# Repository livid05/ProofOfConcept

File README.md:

<div align="center">

# Per-Key Precision

### A fast, low-power TMR analog keyboard on the STM32U5A5

From an RP2040 QMK macro pad to a from-scratch firmware, with every board, measurement and mistake written down.

[Quick start](#quick-start) | [Results](#results-so-far) | [The boards](#the-boards) | [Docs](#find-what-you-need) | [Roadmap](#whats-next) | [License](#license)

</div>

---

## What this is

A capstone project to build a keyboard that senses how far each key is pressed, using TMR (tunnel magnetoresistance) sensors, and reports it to a PC over USB at 8 kHz. The firmware is written from scratch for an STM32U5A5, replacing an earlier QMK proof of concept on an RP2040. The goals are speed, a reliable connection, low power draw and a robust feature set.

This repository holds everything: the firmware, the KiCad hardware for every board revision, the bench results, the research, the presentations, and the reasoning behind each decision.

## How it works

```mermaid
flowchart LR
    A[15 TMR2615D sensors] --> B[CD74HC4067 analog mux]
    B --> C[RC filter 100 ohm + 4.7 nF]
    C --> D[STM32U5A5 ADC1 on PC4]
    D --> E[Press logic and rapid trigger]
    E --> F[USB HID, 8 kHz]
    F --> G[PC]
```

Each sensor outputs a voltage that moves as a magnet gets closer. One 16-way mux feeds a single ADC pin, so the firmware scans the keys one after another. At 8 kHz a full scan has to finish in 125 microseconds. The simple blocking scan takes 730 microseconds for 16 inputs, so a faster pipelined scan has been written; it is the next thing to test on the board. [How the sensing works](docs/03-tmr-sensing-guide.md) explains the details in plain language.

## Results so far

| What | Result | Status |
|---|---|---|
| USB report rate | 7999 reports per second, 0 dropped in 10 seconds | Measured on a PC |
| TMR numpad self-test | 14 of 15 keys pass | Observed on the bench; key K4 is open and parked |
| Blocking scan time | 730 microseconds for 16 inputs | Measured; too slow for 8 kHz |
| Fast pipelined scan with rapid trigger | Written, passes PC tests and a syntax check | Not yet built for the board or run on hardware |
| Full tri-mode keyboard (TriMode60) | Designed through Rev E | Design only, not built |

Things marked as not yet run have not been observed on hardware. The docs keep that difference on purpose. The [bench write-up](docs/04-bench-bringup-2026-11-18.md) has the numbers and how each problem was found.

## The boards

| Board | Purpose | Layers | Status |
|---|---|---|---|
| [Dev board Rev K](hardware/devboard-u5a5/RevK/) | STM32U5A5 development board with USB-C, SWD, a 16-channel mux and a sensor header | 4 | Built and in use |
| [Numpad TMR1 Rev E](hardware/numpad-tmr/RevE/) | 15 TMR sensors in a numpad layout, wired to the dev board | 2 | Built, 14 of 15 keys pass |
| [TriMode60 Rev E](hardware/trimode60/RevE/) | 61 sensors, USB, Bluetooth LE and 2.4 GHz radio in one board | 4 | Designed, not built |

Every revision of every board has notes on what changed and why, with before and after pictures, in [Hardware evolution](docs/02-hardware-evolution.md).

## Quick start

You need a Windows PC with STM32CubeIDE installed (the scripts use the compiler and tools that come with it), VS Code, and the dev board plus numpad.

**1. Build the firmware**

```powershell
cd stm32u5a5-keypad
.\tools\build.ps1
```

**2. Flash over USB**

Connect the dev board with a data cable, hold BOOT, tap RST, release BOOT, then:

```powershell
.\tools\flash-usb.ps1
```

Press RST afterwards. Prebuilt images are in [`binaries/`](binaries/) if you only want to flash.

**3. Run the PC tests (no board needed)**

```powershell
.\tools\test-host.ps1
```

**4. Try the TMR fast-scan image** (not yet run on hardware)

```powershell
cd future_work\2026-11-18_tmr_fast\tools
.\build-tmr-fast.ps1
.\flash-tmr-fast-usb.ps1
.\tmr-console.ps1
```

In the console press `t` for the self-test, then `x` for the sweep that measures noise. Full steps, ports and troubleshooting are in the [Build, flash and test guide](docs/05-build-flash-test-guide.md).

## Find what you need

| I want to... | Read |
|---|---|
| Understand the whole story | [Project story](docs/01-project-story.md) |
| See how the boards changed | [Hardware evolution](docs/02-hardware-evolution.md) |
| Learn how the sensors and ADC work | [TMR sensing guide](docs/03-tmr-sensing-guide.md) |
| See what was measured and what broke | [Bench bring-up](docs/04-bench-bringup-2026-11-18.md) |
| Build, flash and test | [Build, flash and test guide](docs/05-build-flash-test-guide.md) |
| Compare with other 8K TMR keyboards | [8 kHz scanning and market research](docs/06-8k-scanning-and-market-research.md) |
| Know what comes next | [Roadmap](docs/07-roadmap.md) |
| Avoid my mistakes | [Lessons learned](docs/08-lessons-learned.md) |
| Open or order the KiCad boards | [KiCad guide](docs/09-kicad-guide.md) |
| Find a presentation or report | [Presentations and reports](docs/10-presentations-and-reports.md) |
| See how it started on the RP2040 | [RP2040 proof of concept](docs/rp2040-proof-of-concept.md) |

## What is in the repository

| Folder | Contents |
|---|---|
| [`stm32u5a5-keypad/`](stm32u5a5-keypad/) | The firmware, PC tests, build tools and the diagnostic test images. Its `docs/STATUS.md` is the day-to-day status |
| [`hardware/`](hardware/) | KiCad projects, production files and revision notes for all three boards |
| [`docs/`](docs/) | The guides listed above |
| [`reports/`](reports/) | Presentations, the Rev H overview, instructor feedback and the capstone deck source |
| [`binaries/`](binaries/) | Prebuilt `.bin` and `.hex` images of each verified step |
| [`cubemx/`](cubemx/) | STM32CubeMX configuration files |
| [`rp2040-reference/`](rp2040-reference/) | Material from the RP2040 stage |
| Repo root, [`ble_bridge/`](ble_bridge/), [`esb_bridge/`](esb_bridge/), [`esb_dongle/`](esb_dongle/), [`schematics/`](schematics/) | The original RP2040 QMK keypad, its wireless bridges and early schematics |

## What's next

1. Replace the open sensor on key K4 and recheck columns 3 and 4 of the matrix.
2. Build and run the fast scan image on the board, then read the noise sweep.
3. Tune the press thresholds and rapid trigger from real data.
4. Add low-power modes and measure current draw.
5. Build TriMode60 and bring up the radio.

The full ordered list, with reasons, is in the [Roadmap](docs/07-roadmap.md).

## License

Code and hardware designs are MIT, documentation and images are CC BY 4.0, and the reports in `reports/` are all rights reserved. ST and Arm code keeps its own licenses, and the QMK-based RP2040 files are GPL-2.0-or-later. The USB ID 0483:5710 used for bench work is ST's demonstration ID and must be replaced before any product is shared or sold. The exact terms are in [`LICENSE`](LICENSE).

<div align="center">

Made by Tyler Judkins, computer engineering technology, Central Connecticut State University

</div>

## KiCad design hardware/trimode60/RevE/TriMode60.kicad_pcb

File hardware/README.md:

# Hardware

KiCad projects, production files and revision notes. Open the `.kicad_pro` files in KiCad 9 or later. Library tables and the custom TMR2615D symbol and footprint are included with the numpad project.

## Latest revisions

| Folder | Board | Revision | Notes |
|---|---|---|---|
| `devboard-u5a5/RevK/` | STM32U5A5 development board, 4 layers, on-board 16:1 mux and 2x10 sensor header (J8), USB-C high speed | K | `production/` holds gerbers, BOM and positions. Read `README_REVK.txt` first |
| `numpad-tmr/RevE/` | 15-key TMR numpad, 2 layers, hot-swap MX sockets, SK6812 LEDs | E | Production variants: `production`, `production_economic`, `production_economic_handsolder`, `production_jlc_fixed`; each has a README |
| `trimode60/RevE/` | 60% tri-mode keyboard (STM32U595, nRF52840 module, charger, PD sink), 4 layers | E | Design only. Per-sheet schematics: `mcu`, `power`, `keys`, `radio`. Renders in `renders/` |

Hand-solder parts are listed in each board's README (for the dev board: J2, J3, J8, J9, J10; for the numpad: J1, J2, J3). The sensors (U1 to U15 on the numpad) have no LCSC number and are fitted by hand.

## History

[`history/`](history/) holds the README or change notes for each earlier revision (dev board B to J, numpad B to D, TriMode60 A to D, and the panel experiment). They are the source for [docs/02-hardware-evolution.md](../docs/02-hardware-evolution.md).

## Images

[`images/`](images/) holds layout comparisons and renders exported from the KiCad projects during each revision, grouped by board.

| Image | Shows |
|---|---|
| `images/devboard/RevB_layout.png`, `RevC_layout.png`, `RevD_layout.png` | Early layouts: MCU move, on-board mux, stabilizer pins |
| `images/devboard/RevI_vs_RevH_top.png`, `RevJ_vs_RevI_USB.png`, `RevH_UART_before_after.png` | Later layout changes |
| `images/numpad/sensor_before_after.png`, `vip_cleanup_before_after.png`, `vip_cleanup_details.png`, `j2_check.png` | Sensor footprint fix and via-in-pad cleanup |
| `images/trimode60/TriMode60_*.png` | 3D renders and copper layers of Rev E |
| `images/panel/RENDER_top.png`, `RENDER_bottom.png` | The dev board plus numpad panel experiment |

These are not schematic exports. To get schematic PDFs or fresh board renders, run KiCad's export on the projects above.

## Earlier work

The `schematics/` folder at the repository root holds the earlier KiCad projects from the RP2040 stage (capstone design, matrix and mux, numpad TMR1 first version). They are kept for the record; the folders here supersede them.

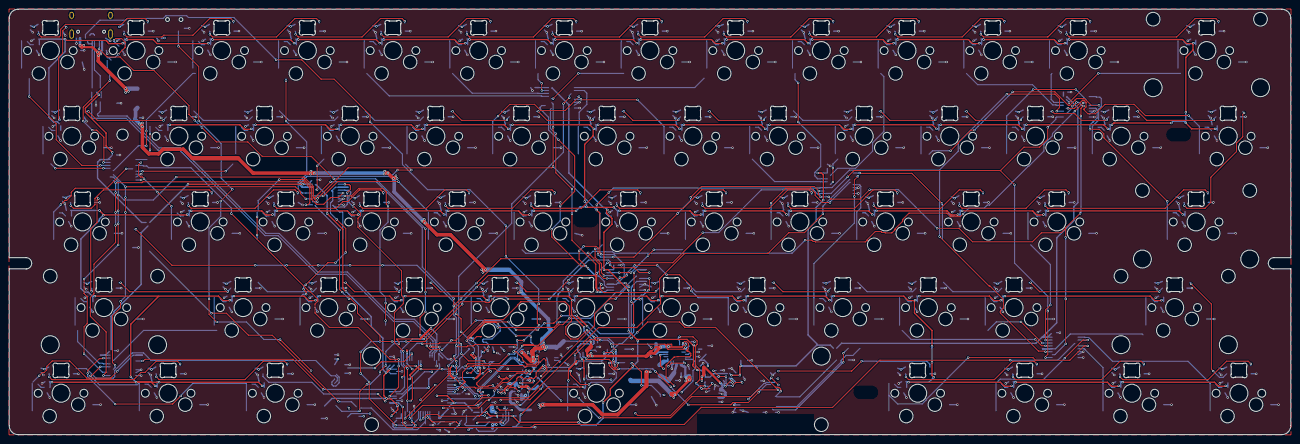
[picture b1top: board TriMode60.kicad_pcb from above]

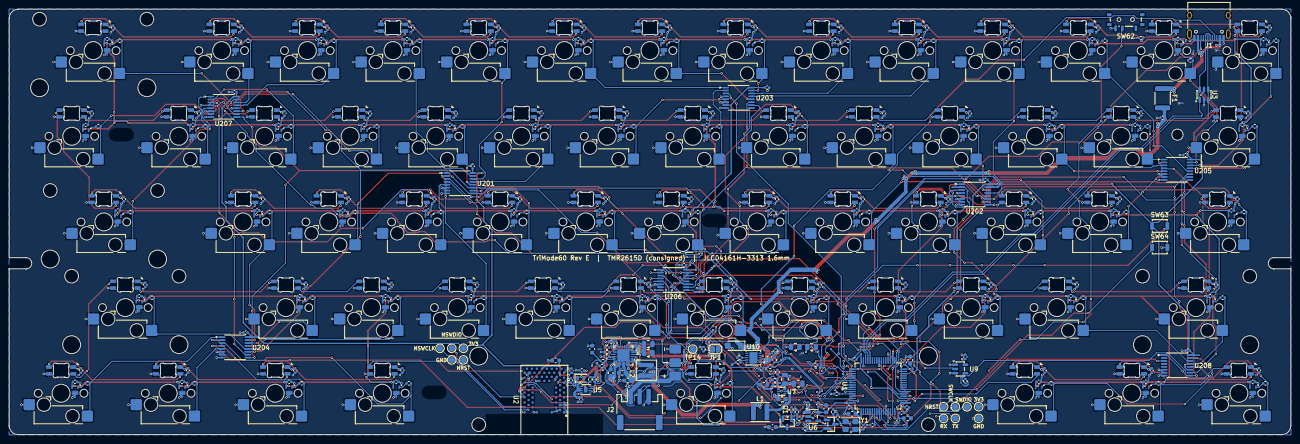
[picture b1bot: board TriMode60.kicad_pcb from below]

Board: 4 copper layers, 285.0 x 94.6 mm, 492 parts (483 on the bottom side), 252 nets.

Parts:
BAT_OUTLINE: LiPo 606090 4000mAh (fit check); Battery_LiPo_606090_Outline
C1, C2, C5, C6, C7, C25, C38, C44: 1uF; C_0402_1005Metric
C3, C4, C8, C9, C15, C32, C41: 10uF; C_0603_1608Metric
C10, C11, C13, C14: 22uF; C_0805_2012Metric
C20, C21, C22, C23, C26, C28, C31, C33, C37, C101, C102, C103, C104, C105, C106, C107, C108, C109, C110, C111, C112, C113, C114, C115, C116, C117, C118, C119, C120, C121, C122, C123, C124, C125, C126, C127, C128, C129, C130, C131, C132, C133, C134, C135, C136, C137, C138, C139, C140, C141, C142, C143, C144, C145, C146, C147, C148, C149, C150, C151, C152, C153, C154, C155, C156, C157, C158, C159, C160, C161, C201, C202, C203, C204, C205, C206, C207, C208, C209, C210, C211, C212, C213, C214, C215, C216, C217, C218, C219, C220, C221, C222, C223, C224, C225, C226, C227, C228, C229, C230, C231, C232, C233, C234, C235, C236, C237, C238, C239, C240, C241, C242, C243, C244, C245, C246, C247, C248, C249, C250, C251, C252, C253, C254, C255, C256, C257, C258, C259, C260, C261, C301, C302, C303, C304, C305, C306, C307, C308: 100nF; C_0402_1005Metric
C24, C27, C42: 4.7uF; C_0603_1608Metric
C29, C30: 12pF; C_0402_1005Metric
C34, C35: 20pF; C_0402_1005Metric
C36: 150pF; C_0603_1608Metric
C39, C40: 10uF 25V; C_0805_2012Metric
C43: 47nF; C_0402_1005Metric
D1, D2, D3, D4, D5, D6, D7, D8, D9, D10, D11, D12, D13, D14, D15, D16, D17, D18, D19, D20, D21, D22, D23, D24, D25, D26, D27, D28, D29, D30, D31, D32, D33, D34, D35, D36, D37, D38, D39, D40, D41, D42, D43, D44, D45, D46, D47, D48, D49, D50, D51, D52, D53, D54, D55, D56, D57, D58, D59, D60, D61: SK6812MINI-E; LED_SK6812MINI-E_Reverse
D62: BAT54C; SOT-23
D63: SMF12A; D_SMF
F1: PTC 3A hold; Fuse_1812_4532Metric
FB1: 600R@100MHz; L_0603_1608Metric
H1: MountingHole_2.5mm_NPTH
H2, H3, H4: MountingSlot_5.0x2.5mm_NPTH
J1: USB-C 16P; USB_C_Receptacle_HRO_TYPE-C-31-M-12
J2: Battery JST-PH 3P; JST_PH_S3B-PH-SM4-TB_1x03-1MP_P2.00mm_Horizontal
J3: Battery pads; Battery_SolderPads_3x
JP1: NTC bypass; SolderJumper-2_P1.3mm_Open_RoundedPad1.0x1.5mm
L1: 1uH 3.2A; L_Changjiang_FNR4020S
L2: 1uH 8.7A; L_Coilcraft_XAL4020-XXX
Q1: AO3401A; SOT-23
R3: 150R 1%; R_0402_1005Metric
R4: 5.23k 1%; R_0402_1005Metric
R5: 30.1k 1%; R_0402_1005Metric
R6, R18, R19, R28: 100k; R_0402_1005Metric
R7, R22, R24, R27, R32: 10k; R_0402_1005Metric
R10, R11: 4.7k; R_0402_1005Metric
R13, R14, R25: 1M 1%; R_0402_1005Metric
R15: 150k 1%; R_0402_1005Metric
R23: 33R; R_0402_1005Metric
R26: 4.3M 1%; R_0402_1005Metric
R29: 47k; R_0402_1005Metric
R33: 6.04k 1%; R_0402_1005Metric
R34: 10.5k 1%; R_0402_1005Metric
R101, R102, R103, R104, R105, R106, R107, R108, R109, R110, R111, R112, R113, R114, R115, R116, R117, R118, R119, R120, R121, R122, R123, R124, R125, R126, R127, R128, R129, R130, R131, R132, R133, R134, R135, R136, R137, R138, R139, R140, R141, R142, R143, R144, R145, R146, R147, R148, R149, R150, R151, R152, R153, R154, R155, R156, R157, R158, R159, R160, R161: 3.3k; R_0402_1005Metric
ST_Backspace: Stab_MX_PCB_2.00u
ST_Enter: Stab_MX_PCB_2.00u
ST_LShift: Stab_MX_PCB_2.00u
ST_RShift: Stab_MX_PCB_2.00u
ST_Space: Stab_MX_PCB_6.25u_Rotated
SW1, SW2, SW3, SW4, SW5, SW6, SW7, SW8, SW9, SW10, SW11, SW12, SW13, SW14, SW15, SW16, SW17, SW18, SW19, SW20, SW21, SW22, SW23, SW24, SW25, SW26, SW27, SW28, SW29, SW30, SW31, SW32, SW33, SW34, SW35, SW36, SW37, SW38, SW39, SW40, SW41, SW42, SW43, SW44, SW45, SW46, SW47, SW48, SW49, SW50, SW51, SW52, SW53, SW54, SW55, SW56, SW57, SW58, SW59, SW60, SW61: CPG151101S11; SW_MX_Hotswap_Kailh_Magnetic_1u
SW62: Power MSK12C02; SW_SPDT_Shouhan_MSK12C02
SW63: BOOT; SW_SPST_B3U-1000P
SW64: RESET; SW_SPST_B3U-1000P
TP1, TP9: 3V3; TestPoint_Pad_D1.5mm
TP2: SWDIO; TestPoint_Pad_D1.5mm
TP3: SWCLK; TestPoint_Pad_D1.5mm
TP4, TP12: NRST; TestPoint_Pad_D1.5mm
TP5, TP13: GND; TestPoint_Pad_D1.5mm
TP7: TX; TestPoint_Pad_D1.5mm
TP8: RX; TestPoint_Pad_D1.5mm
TP10: NSWDIO; TestPoint_Pad_D1.5mm
TP11: NSWCLK; TestPoint_Pad_D1.5mm
TP14: QON; TestPoint_Pad_D1.5mm
U1: STM32U595RJT6; LQFP-64_10x10mm_P0.5mm
U2: BMD-340-A-R-10; u-blox_BMD-340
U3: USBLC6-2SC6; SOT-23-6
U4: BQ25895RTWR; Texas_RTW_WQFN-24-1EP_4x4mm_P0.5mm_EP2.7x2.7mm
U5: MAX17048G+T10; TDFN-8-1EP_2x2mm_P0.5mm_EP0.8x1.2mm
U6: RT9080-33GJ5; TSOT-23-5
U7: TPS61023DRLR; SOT-563
U9: SN74LV1T125DBVR; SOT-23-5
U10: HUSB238_002DD; WDFN-10-1EP_3x3mm_P0.5mm_EP1.8x2.5mm
U101, U102, U103, U104, U105, U106, U107, U108, U109, U110, U111, U112, U113, U114, U115, U116, U117, U118, U119, U120, U121, U122, U123, U124, U125, U126, U127, U128, U129, U130, U131, U132, U133, U134, U135, U136, U137, U138, U139, U140, U141, U142, U143, U144, U145, U146, U147, U148, U149, U150, U151, U152, U153, U154, U155, U156, U157, U158, U159, U160, U161: TMR2615D-ACC-1.000-500; TMR2615D_DFN3L_2x2mm
U201, U202, U203, U204, U205, U206, U207, U208: CD74HC4051PWR; TSSOP-16_4.4x5mm_P0.65mm
Y1: 16MHz; Crystal_SMD_3225-4Pin_3.2x2.5mm
Y2: 32.768kHz; Crystal_SMD_2012-2Pin_2.0x1.2mm

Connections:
+3V3: C7.1, C8.1, C20.1, C21.1, C22.1, C23.1, C24.1, C32.1, C33.1, C301.1, C302.1, C303.1, C304.1, C305.1, C306.1, C307.1, C308.1, FB1.1, Q1.2, R7.2, R10.2, R11.2, R19.2, SW63.1, TP1.1, TP9.1, U1.1, U1.19, U1.32, U1.48, U1.64, U2.17, U2.65, U3.5, U6.5, U201.16, U202.16, U203.16, U204.16, U205.16, U206.16, U207.16, U208.16
/Keys/KEY1: R101.2, SW1.2, U205.14
/Keys/KEY2: R102.2, SW2.2, U205.15
/Keys/KEY3: R103.2, SW3.2, U205.12
/Keys/KEY4: R104.2, SW4.2, U202.13
/Keys/KEY5: R105.2, SW5.2, U203.13
/Keys/KEY6: R106.2, SW6.2, U203.14
/Keys/KEY7: R107.2, SW7.2, U203.15
/Keys/KEY8: R108.2, SW8.2, U203.12
/Keys/KEY9: R109.2, SW9.2, U203.1
/Keys/KEY10: R110.2, SW10.2, U201.14
/Keys/KEY11: R111.2, SW11.2, U201.15
/Keys/KEY12: R112.2, SW12.2, U207.13
/Keys/KEY13: R113.2, SW13.2, U207.14
/Keys/KEY14: R114.2, SW14.2, U207.15
/Keys/KEY15: R115.2, SW15.2, U205.13
/Keys/KEY16: R116.2, SW16.2, U205.1
/Keys/KEY17: R117.2, SW17.2, U205.5
/Keys/KEY18: R118.2, SW18.2, U202.14
/Keys/KEY19: R119.2, SW19.2, U202.15
/Keys/KEY20: R120.2, SW20.2, U203.4
/Keys/KEY21: R121.2, SW21.2, U203.2
/Keys/KEY22: R122.2, SW22.2, U203.5
/Keys/KEY23: R123.2, SW23.2, U201.13
/Keys/KEY24: R124.2, SW24.2, U201.12
/Keys/KEY25: R125.2, SW25.2, U207.4
/Keys/KEY26: R126.2, SW26.2, U207.2
/Keys/KEY27: R127.2, SW27.2, U207.1
/Keys/KEY28: R128.2, SW28.2, U207.12
/Keys/KEY29: R129.2, SW29.2, U205.4
/Keys/KEY30: R130.2, SW30.2, U205.2
/Keys/KEY31: R131.2, SW31.2, U202.4
/Keys/KEY32: R132.2, SW32.2, U202.1
/Keys/KEY33: R133.2, SW33.2, U202.12
/Keys/KEY34: R134.2, SW34.2, U206.13
/Keys/KEY35: R135.2, SW35.2, U206.14
/Keys/KEY36: R136.2, SW36.2, U206.15
/Keys/KEY37: R137.2, SW37.2, U201.4
/Keys/KEY38: R138.2, SW38.2, U201.5
/Keys/KEY39: R139.2, SW39.2, U201.1
/Keys/KEY40: R140.2, SW40.2, U204.15
/Keys/KEY41: R141.2, SW41.2, U207.5
/Keys/KEY42: R142.2, SW42.2, U208.13
/Keys/KEY43: R143.2, SW43.2, U208.14
/Keys/KEY44: R144.2, SW44.2, U202.2
/Keys/KEY45: R145.2, SW45.2, U202.5
/Keys/KEY46: R146.2, SW46.2, U206.4
/Keys/KEY47: R147.2, SW47.2, U206.2
/Keys/KEY48: R148.2, SW48.2, U206.1
/Keys/KEY49: R149.2, SW49.2, U206.12
/Keys/KEY50: R150.2, SW50.2, U201.2
/Keys/KEY51: R151.2, SW51.2, U204.13
/Keys/KEY52: R152.2, SW52.2, U204.14
/Keys/KEY53: R153.2, SW53.2, U204.12
/Keys/KEY54: R154.2, SW54.2, U208.1
/Keys/KEY55: R155.2, SW55.2, U208.12
/Keys/KEY56: R156.2, SW56.2, U208.15
/Keys/KEY57: R157.2, SW57.2, U206.5
/Keys/KEY58: R158.2, SW58.2, U204.4
/Keys/KEY59: R159.2, SW59.2, U204.2
/Keys/KEY60: R160.2, SW60.2, U204.5
/Keys/KEY61: R161.2, SW61.2, U204.1
/Keys/LED_D2: D54.2, D55.3
/Keys/LED_D3: D55.2, D56.3
/Keys/LED_D4: D56.2, D57.3
/Keys/LED_D5: D57.2, D58.3
/Keys/LED_D6: D58.2, D59.3
/Keys/LED_D7: D59.2, D60.3
/Keys/LED_D8: D60.2, D61.3
/Keys/LED_D9: D53.3, D61.2
/Keys/LED_D10: D52.3, D53.2
/Keys/LED_D11: D51.3, D52.2
/Keys/LED_D12: D50.3, D51.2
/Keys/LED_D13: D49.3, D50.2
/Keys/LED_D14: D48.3, D49.2
/Keys/LED_D15: D47.3, D48.2
/Keys/LED_D16: D46.3, D47.2
/Keys/LED_D17: D45.3, D46.2
/Keys/LED_D18: D44.3, D45.2
/Keys/LED_D19: D43.3, D44.2
/Keys/LED_D20: D42.3, D43.2
/Keys/LED_D21: D29.3, D42.2
/Keys/LED_D22: D29.2, D30.3
/Keys/LED_D23: D30.2, D31.3
/Keys/LED_D24: D31.2, D32.3
/Keys/LED_D25: D32.2, D33.3
/Keys/LED_D26: D33.2, D34.3
/Keys/LED_D27: D34.2, D35.3
/Keys/LED_D28: D35.2, D36.3
/Keys/LED_D29: D36.2, D37.3
/Keys/LED_D30: D37.2, D38.3
/Keys/LED_D31: D38.2, D39.3
/Keys/LED_D32: D39.2, D40.3
/Keys/LED_D33: D40.2, D41.3
/Keys/LED_D34: D28.3, D41.2
/Keys/LED_D35: D27.3, D28.2
/Keys/LED_D36: D26.3, D27.2
/Keys/LED_D37: D25.3, D26.2
/Keys/LED_D38: D24.3, D25.2
/Keys/LED_D39: D23.3, D24.2
/Keys/LED_D40: D22.3, D23.2
/Keys/LED_D41: D21.3, D22.2
/Keys/LED_D42: D20.3, D21.2
/Keys/LED_D43: D19.3, D20.2
/Keys/LED_D44: D18.3, D19.2
/Keys/LED_D45: D17.3, D18.2
/Keys/LED_D46: D16.3, D17.2
/Keys/LED_D47: D15.3, D16.2
/Keys/LED_D48: D1.3, D15.2
/Keys/LED_D49: D1.2, D2.3
/Keys/LED_D50: D2.2, D3.3
/Keys/LED_D51: D3.2, D4.3
/Keys/LED_D52: D4.2, D5.3
/Keys/LED_D53: D5.2, D6.3
/Keys/LED_D54: D6.2, D7.3
/Keys/LED_D55: D7.2, D8.3
/Keys/LED_D56: D8.2, D9.3
/Keys/LED_D57: D9.2, D10.3
/Keys/LED_D58: D10.2, D11.3
/Keys/LED_D59: D11.2, D12.3
/Keys/LED_D60: D12.2, D13.3
/Keys/LED_D61: D13.2, D14.3
BOOT0: R22.1, SW63.2, U1.60
BST_FB: C36.2, R14.2, R15.1, R26.2, U7.1
BST_SW: L1.2, U7.5
CC1: J1.A5, U10.4
CC2: J1.B5, U10.5
CHG_BTST: C43.2, U4.21
CHG_CE_N: R6.1, U4.9
CHG_ILIM: R3.1, U4.10
CHG_INT_N: R7.1, U1.57, U4.7
CHG_PMID: C39.1, C40.1, U4.23
CHG_QON: TP14.1, U4.12
CHG_REGN: C42.1, R4.1, U4.22
CHG_SW: C43.1, L2.1, U4.19, U4.20
CHG_TS: J2.2, J3.2, JP1.1, R4.2, R5.1, U4.11
DBG_RX: TP8.1, U1.39
DBG_TX: TP7.1, U1.40
GND: C1.2, C2.2, C3.2, C4.2, C5.2, C6.2, C7.2, C8.2, C9.2, C10.2, C11.2, C13.2, C14.2, C15.2, C20.2, C21.2, C22.2, C23.2, C24.2, C25.2, C26.2, C27.2, C28.2, C29.2, C30.2, C31.2, C32.2, C33.2, C34.2, C35.2, C38.2, C39.2, C40.2, C41.2, C42.2, C44.2, C101.2, C102.2, C103.2, C104.2, C105.2, C106.2, C107.2, C108.2, C109.2, C110.2, C111.2, C112.2, C113.2, C114.2, C115.2, C116.2, C117.2, C118.2, C119.2, C120.2, C121.2, C122.2, C123.2, C124.2, C125.2, C126.2, C127.2, C128.2, C129.2, C130.2, C131.2, C132.2, C133.2, C134.2, C135.2, C136.2, C137.2, C138.2, C139.2, C140.2, C141.2, C142.2, C143.2, C144.2, C145.2, C146.2, C147.2, C148.2, C149.2, C150.2, C151.2, C152.2, C153.2, C154.2, C155.2, C156.2, C157.2, C158.2, C159.2, C160.2, C161.2, C201.2, C202.2, C203.2, C204.2, C205.2, C206.2, C207.2, C208.2, C209.2, C210.2, C211.2, C212.2, C213.2, C214.2, C215.2, C216.2, C217.2, C218.2, C219.2, C220.2, C221.2, C222.2, C223.2, C224.2, C225.2, C226.2, C227.2, C228.2, C229.2, C230.2, C231.2, C232.2, C233.2, C234.2, C235.2, C236.2, C237.2, C238.2, C239.2, C240.2, C241.2, C242.2, C243.2, C244.2, C245.2, C246.2, C247.2, C248.2, C249.2, C250.2, C251.2, C252.2, C253.2, C254.2, C255.2, C256.2, C257.2, C258.2, C259.2, C260.2, C261.2, C301.2, C302.2, C303.2, C304.2, C305.2, C306.2, C307.2, C308.2, D1.4, D2.4, D3.4, D4.4, D5.4, D6.4, D7.4, D8.4, D9.4, D10.4, D11.4, D12.4, D13.4, D14.4, D15.4, D16.4, D17.4, D18.4, D19.4, D20.4, D21.4, D22.4, D23.4, D24.4, D25.4, D26.4, D27.4, D28.4, D29.4, D30.4, D31.4, D32.4, D33.4, D34.4, D35.4, D36.4, D37.4, D38.4, D39.4, D40.4, D41.4, D42.4, D43.4, D44.4, D45.4, D46.4, D47.4, D48.4, D49.4, D50.4, D51.4, D52.4, D53.4, D54.4, D55.4, D56.4, D57.4, D58.4, D59.4, D60.4, D61.4, D63.2, J1.A1, J1.A12, J1.B1, J1.B12, J1.S1, J2.3, J3.3, R3.2, R5.2, R6.2, R13.2, R15.2, R18.2, R22.2, R29.2, R32.2, R33.2, R34.2, SW1.1, SW2.1, SW3.1, SW4.1, SW5.1, SW6.1, SW7.1, SW8.1, SW9.1, SW10.1, SW11.1, SW12.1, SW13.1, SW14.1, SW15.1, SW16.1, SW17.1, SW18.1, SW19.1, SW20.1, SW21.1, SW22.1, SW23.1, SW24.1, SW25.1, SW26.1, SW27.1, SW28.1, SW29.1, SW30.1, SW31.1, SW32.1, SW33.1, SW34.1, SW35.1, SW36.1, SW37.1, SW38.1, SW39.1, SW40.1, SW41.1, SW42.1, SW43.1, SW44.1, SW45.1, SW46.1, SW47.1, SW48.1, SW49.1, SW50.1, SW51.1, SW52.1, SW53.1, SW54.1, SW55.1, SW56.1, SW57.1, SW58.1, SW59.1, SW60.1, SW61.1, SW62.3, SW64.2, TP5.1, TP13.1, U1.12, U1.18, U1.31, U1.47, U1.63, U2.1, U2.2, U2.3, U2.4, U2.5, U2.16, U2.18, U2.29, U2.30, U2.45, U2.46, U2.47, U2.55, U3.2, U4.8, U4.17, U4.18, U4.25, U5.1, U5.4, U5.6, U5.9, U6.2, U7.4, U9.1, U9.3, U10.11, U101.3, U102.3, U103.3, U104.3, U105.3, U106.3, U107.3, U108.3, U109.3, U110.3, U111.3, U112.3, U113.3, U114.3, U115.3, U116.3, U117.3, U118.3, U119.3, U120.3, U121.3, U122.3, U123.3, U124.3, U125.3, U126.3, U127.3, U128.3, U129.3, U130.3, U131.3, U132.3, U133.3, U134.3, U135.3, U136.3, U137.3, U138.3, U139.3, U140.3, U141.3, U142.3, U143.3, U144.3, U145.3, U146.3, U147.3, U148.3, U149.3, U150.3, U151.3, U152.3, U153.3, U154.3, U155.3, U156.3, U157.3, U158.3, U159.3, U160.3, U161.3, U201.6, U201.7, U201.8, U202.6, U202.7, U202.8, U203.6, U203.7, U203.8, U204.6, U204.7, U204.8, U205.6, U205.7, U205.8, U206.6, U206.7, U206.8, U207.6, U207.7, U207.8, U208.6, U208.7, U208.8, Y1.2, Y1.4
HSE_IN: C29.1, U1.5, Y1.1
HSE_OUT: C30.1, U1.6, Y1.3
I2C_SCL: R10.1, U1.58, U4.5, U5.7
I2C_SDA: R11.1, U1.59, U4.6, U5.8
LED_5V: C10.1, C11.1, C13.1, C14.1, C31.1, C36.1, C201.1, C202.1, C203.1, C204.1, C205.1, C206.1, C207.1, C208.1, C209.1, C210.1, C211.1, C212.1, C213.1, C214.1, C215.1, C216.1, C217.1, C218.1, C219.1, C220.1, C221.1, C222.1, C223.1, C224.1, C225.1, C226.1, C227.1, C228.1, C229.1, C230.1, C231.1, C232.1, C233.1, C234.1, C235.1, C236.1, C237.1, C238.1, C239.1, C240.1, C241.1, C242.1, C243.1, C244.1, C245.1, C246.1, C247.1, C248.1, C249.1, C250.1, C251.1, C252.1, C253.1, C254.1, C255.1, C256.1, C257.1, C258.1, C259.1, C260.1, C261.1, D1.1, D2.1, D3.1, D4.1, D5.1, D6.1, D7.1, D8.1, D9.1, D10.1, D11.1, D12.1, D13.1, D14.1, D15.1, D16.1, D17.1, D18.1, D19.1, D20.1, D21.1, D22.1, D23.1, D24.1, D25.1, D26.1, D27.1, D28.1, D29.1, D30.1, D31.1, D32.1, D33.1, D34.1, D35.1, D36.1, D37.1, D38.1, D39.1, D40.1, D41.1, D42.1, D43.1, D44.1, D45.1, D46.1, D47.1, D48.1, D49.1, D50.1, D51.1, D52.1, D53.1, D54.1, D55.1, D56.1, D57.1, D58.1, D59.1, D60.1, D61.1, R14.1, U7.6, U9.5
LED_D1: D54.3, R23.2
LED_DATA: U1.36, U9.2
LED_DATA_5V: R23.1, U9.4
LED_PWR_EN: R18.1, U1.35, U7.2
LED_VADJ: C38.1, R26.1, R27.2
LED_VADJ_PWM: R27.1, U1.62
MUX_OUT1: U1.14, U201.3
MUX_OUT2: U1.15, U202.3
MUX_OUT3: U1.16, U203.3
MUX_OUT4: U1.17, U204.3
MUX_OUT5: U1.20, U205.3
MUX_OUT6: U1.21, U206.3
MUX_OUT7: U1.22, U207.3
MUX_OUT8: U1.23, U208.3
MUX_S0: U1.8, U201.11, U202.11, U203.11, U204.11, U205.11, U206.11, U207.11, U208.11
MUX_S1: U1.9, U201.10, U202.10, U203.10, U204.10, U205.10, U206.10, U207.10, U208.10
MUX_S2: U1.10, U201.9, U202.9, U203.9, U204.9, U205.9, U206.9, U207.9, U208.9
NRF_CS: U1.50, U2.35
NRF_IRQ: U1.54, U2.31
NRF_MISO: U1.52, U2.34
NRF_MOSI: U1.53, U2.33
NRF_RST_N: TP12.1, U1.56, U2.39
NRF_SCK: U1.51, U2.32
NRF_SWCLK: TP11.1, U2.43
NRF_SWDIO: TP10.1, U2.44
NRST: C28.1, SW64.1, TP4.1, U1.7
NTC_SUB: JP1.2, R32.1
unnamed: R101.1, U101.1
unnamed: R102.1, U102.1
unnamed: R103.1, U103.1
unnamed: R104.1, U104.1
unnamed: R105.1, U105.1
unnamed: R106.1, U106.1
unnamed: R107.1, U107.1
unnamed: R108.1, U108.1
unnamed: R109.1, U109.1
unnamed: R110.1, U110.1
unnamed: R111.1, U111.1
unnamed: R112.1, U112.1
unnamed: R113.1, U113.1
unnamed: R114.1, U114.1
unnamed: R115.1, U115.1
unnamed: R116.1, U116.1
unnamed: R117.1, U117.1
unnamed: R118.1, U118.1
unnamed: R119.1, U119.1
unnamed: R120.1, U120.1
unnamed: R121.1, U121.1
unnamed: R122.1, U122.1
unnamed: R123.1, U123.1
unnamed: R124.1, U124.1
unnamed: R125.1, U125.1
unnamed: R126.1, U126.1
unnamed: R127.1, U127.1
unnamed: R128.1, U128.1
unnamed: R129.1, U129.1
unnamed: R130.1, U130.1
unnamed: R131.1, U131.1
unnamed: R132.1, U132.1
unnamed: R133.1, U133.1
unnamed: R134.1, U134.1
unnamed: R135.1, U135.1
unnamed: R136.1, U136.1
unnamed: R137.1, U137.1
unnamed: R138.1, U138.1
unnamed: R139.1, U139.1
unnamed: R140.1, U140.1
unnamed: R141.1, U141.1
unnamed: R142.1, U142.1
unnamed: R143.1, U143.1
unnamed: R144.1, U144.1
unnamed: R145.1, U145.1
unnamed: R146.1, U146.1
unnamed: R147.1, U147.1
unnamed: R148.1, U148.1
unnamed: R149.1, U149.1
unnamed: R150.1, U150.1
unnamed: R151.1, U151.1
unnamed: R152.1, U152.1
unnamed: R153.1, U153.1
unnamed: R154.1, U154.1
unnamed: R155.1, U155.1
unnamed: R156.1, U156.1
unnamed: R157.1, U157.1
unnamed: R158.1, U158.1
unnamed: R159.1, U159.1
unnamed: R160.1, U160.1
unnamed: R161.1, U161.1
PD_ISET: R34.1, U10.9
PD_VSET: R33.1, U10.8
PWR_EN: D62.3, R13.1, U6.3
PWR_SW: D62.2, R25.1, SW62.2
SENS_3V3: C15.1, C37.2, C101.1, C102.1, C103.1, C104.1, C105.1, C106.1, C107.1, C108.1, C109.1, C110.1, C111.1, C112.1, C113.1, C114.1, C115.1, C116.1, C117.1, C118.1, C119.1, C120.1, C121.1, C122.1, C123.1, C124.1, C125.1, C126.1, C127.1, C128.1, C129.1, C130.1, C131.1, C132.1, C133.1, C134.1, C135.1, C136.1, C137.1, C138.1, C139.1, C140.1, C141.1, C142.1, C143.1, C144.1, C145.1, C146.1, C147.1, C148.1, C149.1, C150.1, C151.1, C152.1, C153.1, C154.1, C155.1, C156.1, C157.1, C158.1, C159.1, C160.1, C161.1, Q1.3, U101.2, U102.2, U103.2, U104.2, U105.2, U106.2, U107.2, U108.2, U109.2, U110.2, U111.2, U112.2, U113.2, U114.2, U115.2, U116.2, U117.2, U118.2, U119.2, U120.2, U121.2, U122.2, U123.2, U124.2, U125.2, U126.2, U127.2, U128.2, U129.2, U130.2, U131.2, U132.2, U133.2, U134.2, U135.2, U136.2, U137.2, U138.2, U139.2, U140.2, U141.2, U142.2, U143.2, U144.2, U145.2, U146.2, U147.2, U148.2, U149.2, U150.2, U151.2, U152.2, U153.2, U154.2, U155.2, U156.2, U157.2, U158.2, U159.2, U160.2, U161.2
SENS_EN_N: R24.1, U1.34
SENS_GATE: C37.1, Q1.1, R19.1, R24.2
SWCLK: TP3.1, U1.49
SWDIO: TP2.1, U1.46
USB_DM: J1.A7, J1.B7, U1.44, U3.3, U3.4
USB_DP: J1.A6, J1.B6, U1.45, U3.1, U3.6
VBAT: C4.1, C5.1, J2.1, J3.1, U4.13, U4.14, U5.2, U5.3
VBUS: C1.1, C2.1, C44.1, D63.1, F1.2, R28.1, U4.1, U10.1
VBUS_C: F1.1, J1.A4, J1.A9, J1.B4, J1.B9
VBUS_EN: D62.1, R28.2, R29.1
VCAP: C27.1, U1.30
VDDA: C25.1, C26.1, FB1.2, U1.13
VSYS: C3.1, C6.1, C9.1, C41.1, L1.1, L2.2, R25.2, U4.15, U4.16, U6.1, U7.3
XL1: C34.1, U2.13, Y2.1
XL2: C35.1, U2.14, Y2.2

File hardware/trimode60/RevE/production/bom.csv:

Comment,Designator,Footprint,LCSC Part #
1uF,"C1,C2,C5,C6,C7,C25,C38,C44",C_0402_1005Metric,C52923
10uF,"C3,C4,C8,C9,C15,C32,C41",C_0603_1608Metric,C19702
22uF,"C10,C11,C13,C14",C_0805_2012Metric,C45783
100nF,"C20,C21,C22,C23,C26,C28,C31,C33,C37,C101,C102,C103,C104,C105,C106,C107,C108,C109,C110,C111,C112,C113,C114,C115,C116,C117,C118,C119,C120,C121,C122,C123,C124,C125,C126,C127,C128,C129,C130,C131,C132,C133,C134,C135,C136,C137,C138,C139,C140,C141,C142,C143,C144,C145,C146,C147,C148,C149,C150,C151,C152,C153,C154,C155,C156,C157,C158,C159,C160,C161,C201,C202,C203,C204,C205,C206,C207,C208,C209,C210,C211,C212,C213,C214,C215,C216,C217,C218,C219,C220,C221,C222,C223,C224,C225,C226,C227,C228,C229,C230,C231,C232,C233,C234,C235,C236,C237,C238,C239,C240,C241,C242,C243,C244,C245,C246,C247,C248,C249,C250,C251,C252,C253,C254,C255,C256,C257,C258,C259,C260,C261,C301,C302,C303,C304,C305,C306,C307,C308",C_0402_1005Metric,C1525
4.7uF,"C24,C27,C42",C_0603_1608Metric,C19666
12pF,"C29,C30",C_0402_1005Metric,C1547
20pF,"C34,C35",C_0402_1005Metric,C1554
150pF,C36,C_0603_1608Metric,C37298
10uF 25V,"C39,C40",C_0805_2012Metric,C15850
47nF,C43,C_0402_1005Metric,C285062
SK6812MINI-E,"D1,D2,D3,D4,D5,D6,D7,D8,D9,D10,D11,D12,D13,D14,D15,D16,D17,D18,D19,D20,D21,D22,D23,D24,D25,D26,D27,D28,D29,D30,D31,D32,D33,D34,D35,D36,D37,D38,D39,D40,D41,D42,D43,D44,D45,D46,D47,D48,D49,D50,D51,D52,D53,D54,D55,D56,D57,D58,D59,D60,D61",LED_SK6812MINI-E_Reverse,C5149201
BAT54C,D62,SOT-23,C22466350
SMF12A,D63,D_SMF,C19077506
PTC 3A hold,F1,Fuse_1812_4532Metric,C883162
600R@100MHz,FB1,L_0603_1608Metric,C1002
USB-C 16P,J1,USB_C_Receptacle_HRO_TYPE-C-31-M-12,C165948
Battery JST-PH 3P,J2,JST_PH_S3B-PH-SM4-TB_1x03-1MP_P2.00mm_Horizontal,C265101
1uH 3.2A,L1,L_Changjiang_FNR4020S,C167822
1uH 8.7A,L2,L_Coilcraft_XAL4020-XXX,C4555951
AO3401A,Q1,SOT-23,C15127
150R 1%,R3,R_0402_1005Metric,C25082
5.23k 1%,R4,R_0402_1005Metric,C2933105
30.1k 1%,R5,R_0402_1005Metric,C29402
100k,"R6,R18,R19,R28",R_0402_1005Metric,C25741
10k,"R7,R22,R24,R27,R32",R_0402_1005Metric,C25744
4.7k,"R10,R11",R_0402_1005Metric,C25900
1M 1%,"R13,R14,R25",R_0402_1005Metric,C26083
150k 1%,R15,R_0402_1005Metric,C25755
33R,R23,R_0402_1005Metric,C25105
4.3M 1%,R26,R_0402_1005Metric,C2998052
47k,R29,R_0402_1005Metric,C25792
6.04k 1%,R33,R_0402_1005Metric,C25913
10.5k 1%,R34,R_0402_1005Metric,C25850
3.3k,"R101,R102,R103,R104,R105,R106,R107,R108,R109,R110,R111,R112,R113,R114,R115,R116,R117,R118,R119,R120,R121,R122,R123,R124,R125,R126,R127,R128,R129,R130,R131,R132,R133,R134,R135,R136,R137,R138,R139,R140,R141,R142,R143,R144,R145,R146,R147,R148,R149,R150,R151,R152,R153,R154,R155,R156,R157,R158,R159,R160,R161",R_0402_1005Metric,C25890
CPG151101S11,"SW1,SW2,SW3,SW4,SW5,SW6,SW7,SW8,SW9,SW10,SW11,SW12,SW13,SW14,SW15,SW16,SW17,SW18,SW19,SW20,SW21,SW22,SW23,SW24,SW25,SW26,SW27,SW28,SW29,SW30,SW31,SW32,SW33,SW34,SW35,SW36,SW37,SW38,SW39,SW40,SW41,SW42,SW43,SW44,SW45,SW46,SW47,SW48,SW49,SW50,SW51,SW52,SW53,SW54,SW55,SW56,SW57,SW58,SW59,SW60,SW61",SW_MX_Hotswap_Kailh_Magnetic_1u,C41430893
Power MSK12C02,SW62,SW_SPDT_Shouhan_MSK12C02,C431540
BOOT,SW63,SW_SPST_B3U-1000P,C231329
RESET,SW64,SW_SPST_B3U-1000P,C231329
STM32U595RJT6,U1,LQFP-64_10x10mm_P0.5mm,C28563722
BMD-340-A-R-10,U2,u-blox_BMD-340,C5456944
USBLC6-2SC6,U3,SOT-23-6,C7519
BQ25895RTWR,U4,Texas_RTW_WQFN-24-1EP_4x4mm_P0.5mm_EP2.7x2.7mm,C80200
MAX17048G+T10,U5,TDFN-8-1EP_2x2mm_P0.5mm_EP0.8x1.2mm,C2682616
RT9080-33GJ5,U6,TSOT-23-5,C841192
TPS61023DRLR,U7,SOT-563,C919459
SN74LV1T125DBVR,U9,SOT-23-5,C473338
HUSB238_002DD,U10,WDFN-10-1EP_3x3mm_P0.5mm_EP1.8x2.5mm,C7471904
TMR2615D-ACC-1.000-500,"U101,U102,U103,U104,U105,U106,U107,U108,U109,U110,U111,U112,U113,U114,U115,U116,U117,U118,U119,U120,U121,U122,U123,U124,U125,U126,U127,U128,U129,U130,U131,U132,U133,U134,U135,U136,U137,U138,U139,U140,U141,U142,U143,U144,U145,U146,U147,U148,U149,U150,U151,U152,U153,U154,U155,U156,U157,U158,U159,U160,U161",TMR2615D_DFN3L_2x2mm,
CD74HC4051PWR,"U201,U202,U203,U204,U205,U206,U207,U208",TSSOP-16_4.4x5mm_P0.65mm,C352826
16MHz,Y1,Crystal_SMD_3225-4Pin_3.2x2.5mm,C13738
32.768kHz,Y2,Crystal_SMD_2012-2Pin_2.0x1.2mm,C97607

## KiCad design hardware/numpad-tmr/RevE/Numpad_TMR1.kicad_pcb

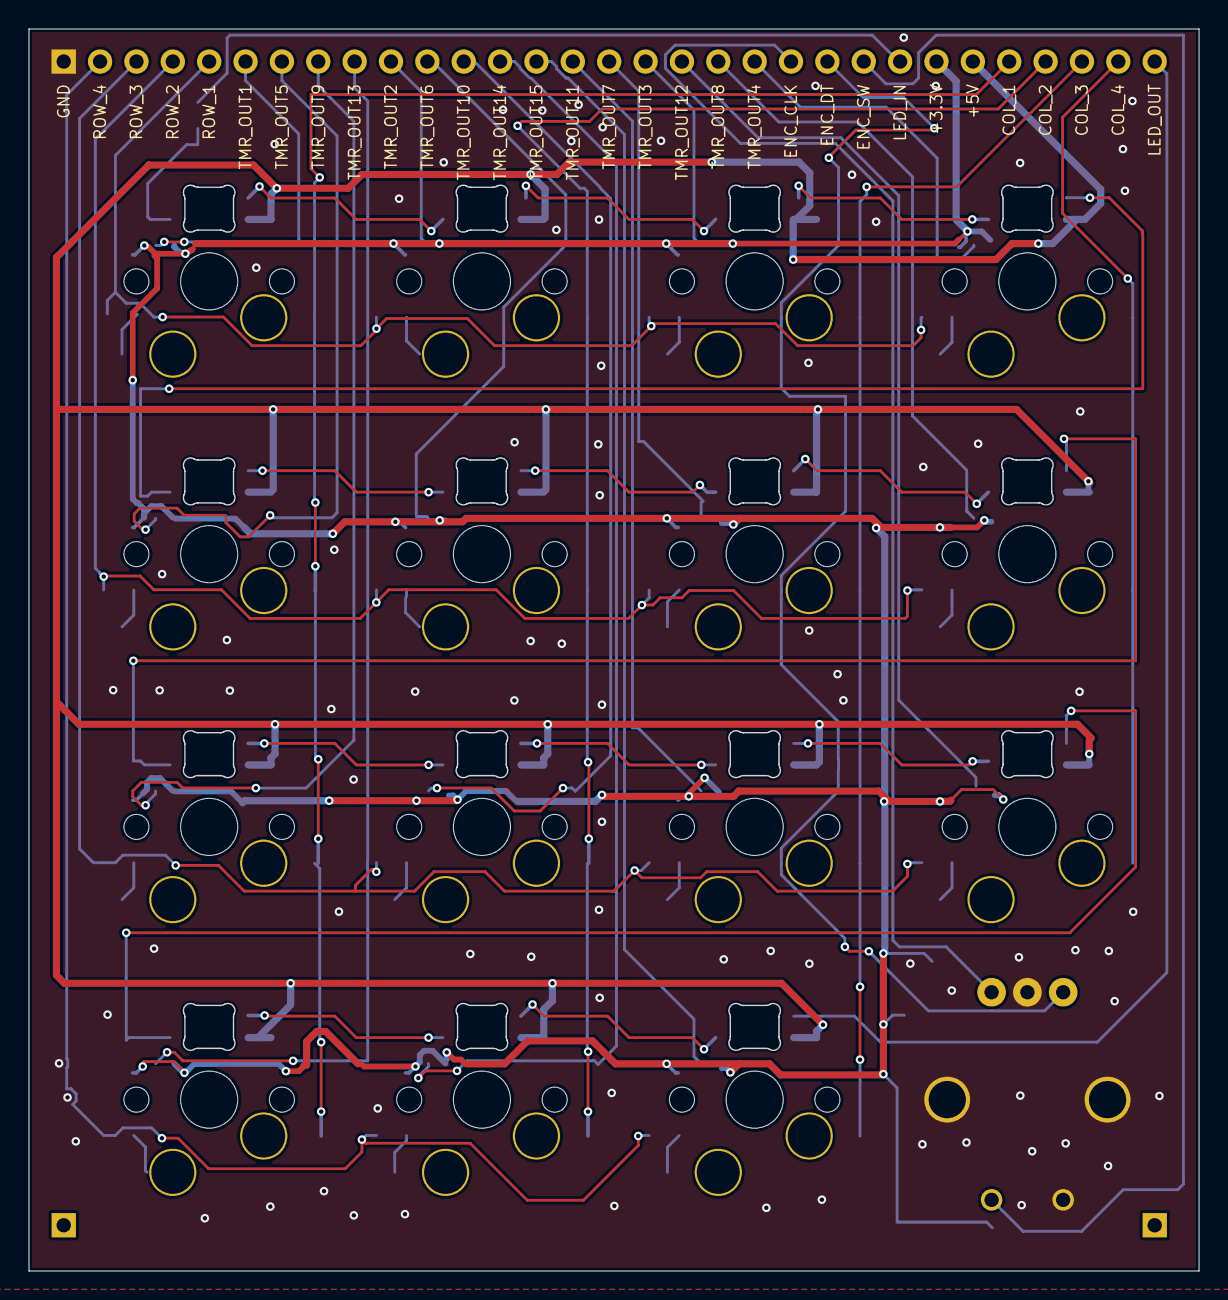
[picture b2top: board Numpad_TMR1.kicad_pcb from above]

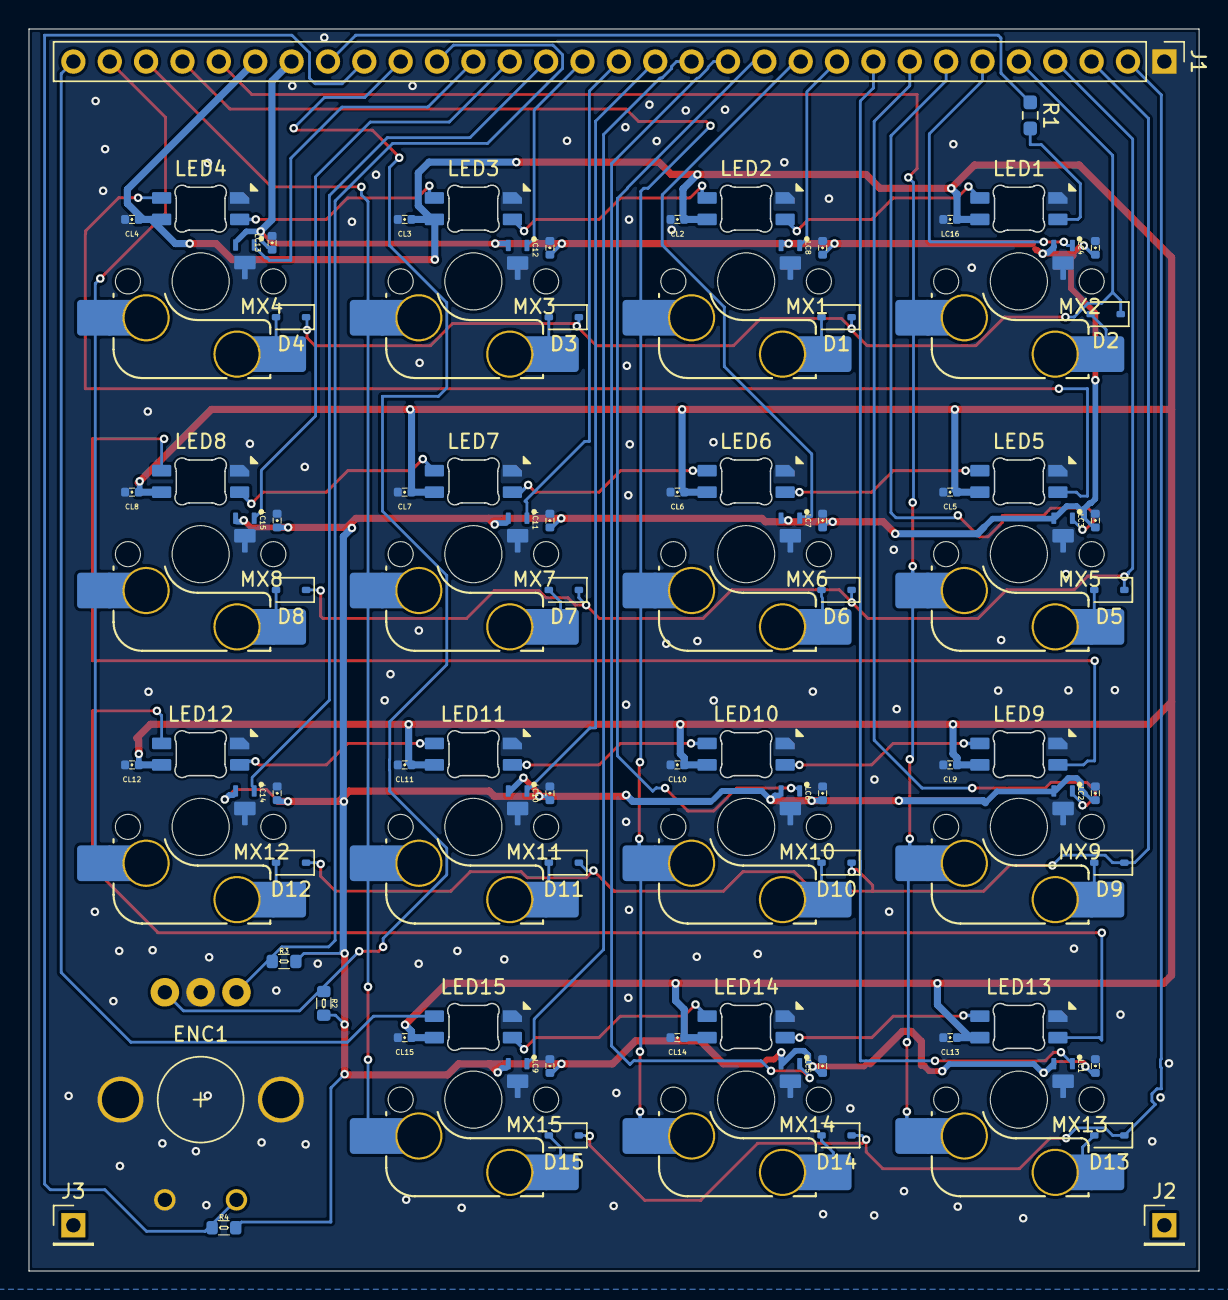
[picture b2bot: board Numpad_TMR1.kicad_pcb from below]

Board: 2 copper layers, 81.7 x 86.7 mm, 98 parts (98 on the bottom side), 61 nets.

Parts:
CL2, CL3, CL4, CL5, CL6, CL7, CL8, CL9, CL10, CL11, CL12, CL13, CL14, CL15: 0.1uF; C_0402
D1, D2, D3, D4, D5, D6, D7, D8, D9, D10, D11, D12, D13, D14, D15: D_Small; D_SOD-323
ENC1: RotaryEncoder_Switch_MP; RotaryEncoder_MX_EC11_CircularMountingHoles
J1: Conn_01x31_Pin; PinHeader_1x31_P2.54mm_Vertical
J2, J3: Conn_01x01_Pin; PinHeader_1x01_P2.54mm_Vertical
LC1, LC2, LC3, LC4, LC5, LC6, LC7, LC8, LC9, LC10, LC11, LC12, LC13, LC14, LC15, LC16: 0.1uF; C_0402
LED1, LED2, LED3, LED4, LED5, LED6, LED7, LED8, LED9, LED10, LED11, LED12, LED13, LED14, LED15: SK6812MINI-E; LED_6028R
MX1, MX2, MX3, MX4, MX5, MX6, MX7, MX8, MX9, MX10, MX11, MX12, MX13, MX14, MX15: MX_SW_HS; SW_MX_HS_CPG151101S11_1u
R1: 330; R_0603_1608Metric_Pad0.98x0.95mm_HandSolder
R2, R3, R4: 10k; R_0603
U1, U2, U3, U4, U5, U6, U7, U8, U9, U10, U11, U12, U13, U14, U15: TMR2615D-ACC-1.000-500; SW_MX_TMR2615D_1u

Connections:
+3.3V: J1.25, LC1.1, LC2.1, LC3.1, LC4.1, LC5.1, LC6.1, LC7.1, LC8.1, LC9.1, LC10.1, LC11.1, LC12.1, LC13.1, LC14.1, LC15.1, R2.2, R3.2, R4.2, U1.2 (VDD), U2.2 (VDD), U3.2 (VDD), U4.2 (VDD), U5.2 (VDD), U6.2 (VDD), U7.2 (VDD), U8.2 (VDD), U9.2 (VDD), U10.2 (VDD), U11.2 (VDD), U12.2 (VDD), U13.2 (VDD), U14.2 (VDD), U15.2 (VDD)
+5V: CL2.1, CL3.1, CL4.1, CL5.1, CL6.1, CL7.1, CL8.1, CL9.1, CL10.1, CL11.1, CL12.1, CL13.1, CL14.1, CL15.1, J1.26, LC16.1, LED1.1 (VDD), LED2.1 (VDD), LED3.1 (VDD), LED4.1 (VDD), LED5.1 (VDD), LED6.1 (VDD), LED7.1 (VDD), LED8.1 (VDD), LED9.1 (VDD), LED10.1 (VDD), LED11.1 (VDD), LED12.1 (VDD), LED13.1 (VDD), LED14.1 (VDD), LED15.1 (VDD)
COL_1: J1.27, MX2.1, MX5.1, MX9.1, MX13.1
COL_2: J1.28, MX1.1, MX6.1, MX10.1, MX14.1
COL_3: J1.29, MX3.1, MX7.1, MX11.1, MX15.1
COL_4: J1.30, MX4.1, MX8.1, MX12.1
ENC_CLK: ENC1.A, J1.21, R3.1
ENC_DT: ENC1.B, J1.22, R2.1
ENC_SW: ENC1.S2, J1.23, R4.1
GND: CL2.2, CL3.2, CL4.2, CL5.2, CL6.2, CL7.2, CL8.2, CL9.2, CL10.2, CL11.2, CL12.2, CL13.2, CL14.2, CL15.2, ENC1.C, ENC1.MP, ENC1.S1, J1.1, LC1.2, LC2.2, LC3.2, LC4.2, LC5.2, LC6.2, LC7.2, LC8.2, LC9.2, LC10.2, LC11.2, LC12.2, LC13.2, LC14.2, LC15.2, LC16.2, LED1.4 (VSS), LED2.4 (VSS), LED3.4 (VSS), LED4.4 (VSS), LED5.4 (VSS), LED6.4 (VSS), LED7.4 (VSS), LED8.4 (VSS), LED9.4 (VSS), LED10.4 (VSS), LED11.4 (VSS), LED12.4 (VSS), LED13.4 (VSS), LED14.4 (VSS), LED15.4 (VSS), U1.3 (GND), U2.3 (GND), U3.3 (GND), U4.3 (GND), U5.3 (GND), U6.3 (GND), U7.3 (GND), U8.3 (GND), U9.3 (GND), U10.3 (GND), U11.3 (GND), U12.3 (GND), U13.3 (GND), U14.3 (GND), U15.3 (GND)
LED_IN: J1.24, R1.1
LED_OUT: J1.31, LED15.2 (DOUT)
unnamed: D1.2 (A), MX1.2
unnamed: D2.2 (A), MX2.2
unnamed: D3.2 (A), MX3.2
unnamed: D4.2 (A), MX4.2
unnamed: D5.2 (A), MX5.2
unnamed: D6.2 (A), MX6.2
unnamed: D7.2 (A), MX7.2
unnamed: D8.2 (A), MX8.2
unnamed: D9.2 (A), MX9.2
unnamed: D10.2 (A), MX10.2
unnamed: D11.2 (A), MX11.2
unnamed: D12.2 (A), MX12.2
unnamed: D13.2 (A), MX13.2
unnamed: D14.2 (A), MX14.2
unnamed: D15.2 (A), MX15.2
unnamed: LED1.3 (DIN), R1.2
unnamed: LED1.2 (DOUT), LED2.3 (DIN)
unnamed: LED2.2 (DOUT), LED3.3 (DIN)
unnamed: LED3.2 (DOUT), LED4.3 (DIN)
unnamed: LED4.2 (DOUT), LED5.3 (DIN)
unnamed: LED5.2 (DOUT), LED6.3 (DIN)
unnamed: LED6.2 (DOUT), LED7.3 (DIN)
unnamed: LED7.2 (DOUT), LED8.3 (DIN)
unnamed: LED8.2 (DOUT), LED9.3 (DIN)
unnamed: LED9.2 (DOUT), LED10.3 (DIN)
unnamed: LED10.2 (DOUT), LED11.3 (DIN)
unnamed: LED11.2 (DOUT), LED12.3 (DIN)
unnamed: LED12.2 (DOUT), LED13.3 (DIN)
unnamed: LED13.2 (DOUT), LED14.3 (DIN)
unnamed: LED14.2 (DOUT), LED15.3 (DIN)
ROW_1: D1.1 (K), D2.1 (K), D3.1 (K), D4.1 (K), J1.5
ROW_2: D5.1 (K), D6.1 (K), D7.1 (K), D8.1 (K), J1.4
ROW_3: D9.1 (K), D10.1 (K), D11.1 (K), D12.1 (K), J1.3
ROW_4: D13.1 (K), D14.1 (K), D15.1 (K), J1.2
TMR_OUT1: J1.6, U1.1 (VOUT)
TMR_OUT2: J1.10, U2.1 (VOUT)
TMR_OUT3: J1.17, U3.1 (VOUT)
TMR_OUT4: J1.20, U4.1 (VOUT)
TMR_OUT5: J1.7, U5.1 (VOUT)
TMR_OUT6: J1.11, U6.1 (VOUT)
TMR_OUT7: J1.16, U7.1 (VOUT)
TMR_OUT8: J1.19, U8.1 (VOUT)
TMR_OUT9: J1.8, U9.1 (VOUT)
TMR_OUT10: J1.12, U10.1 (VOUT)
TMR_OUT11: J1.15, U11.1 (VOUT)
TMR_OUT12: J1.18, U12.1 (VOUT)
TMR_OUT13: J1.9, U13.1 (VOUT)
TMR_OUT14: J1.13, U14.1 (VOUT)
TMR_OUT15: J1.14, U15.1 (VOUT)

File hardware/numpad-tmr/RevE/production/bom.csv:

Comment,Designator,Footprint,LCSC Part #
0.1uF,"CL2, CL3, CL4, CL5, CL6, CL7, CL8, CL9, CL10, CL11, CL12, CL13, CL14, CL15, LC1, LC2, LC3, LC4, LC5, LC6, LC7, LC8, LC9, LC10, LC11, LC12, LC13, LC14, LC15, LC16",C_0402,C1525
D_Small,"D1, D2, D3, D4, D5, D6, D7, D8, D9, D10, D11, D12, D13, D14, D15",D_SOD-323,C2128
RotaryEncoder_Switch_MP,ENC1,RotaryEncoder_MX_EC11_CircularMountingHoles,C255515
SK6812MINI-E,"LED1, LED2, LED3, LED4, LED5, LED6, LED7, LED8, LED9, LED10, LED11, LED12, LED13, LED14, LED15",LED_6028R,C5149201
MX_SW_HS,"MX1, MX2, MX3, MX4, MX5, MX6, MX7, MX8, MX9, MX10, MX11, MX12, MX13, MX14, MX15",SW_MX_HS_CPG151101S11_1u,C41430893
330,R1,R_0603_1608Metric_Pad0.98x0.95mm_HandSolder,C23138
10k,"R2, R3, R4",R_0603,C25804
TMR2615D-ACC-1.000-500,"U1, U2, U3, U4, U5, U6, U7, U8, U9, U10, U11, U12, U13, U14, U15",SW_MX_TMR2615D_1u,
